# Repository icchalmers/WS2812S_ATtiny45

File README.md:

# WS2812S with ATtiny85

This is a small test board for the WS2812S LEDs using the ATtiny85. It was made as part [Fab Academy 2015](http://www.fabacademy.org/) at [Fab Lab Strathclyde](http://www.strath.ac.uk/fablab/). You can follow the process on [my class website](http://fabacademy.org/archives/2015/eu/students/chalmers.iain/index.html). The content is also mirrored to [my GitHub Pages site](http://icchalmers.github.io/).

# Design

The board was designed in KiCad, and machined on a Denford PCB Engraver. The footprints are designed for reflow soldering, but the board should be hand solderable with a steady hand.

All of the parts are part of the standard Fab Lab inventory, with the exception of the WS2812S and the ATtiny85. However, you can substitute an ATtiny45 without any problem. I just used an 85 because a) more memory and b) we actually got them cheaper!

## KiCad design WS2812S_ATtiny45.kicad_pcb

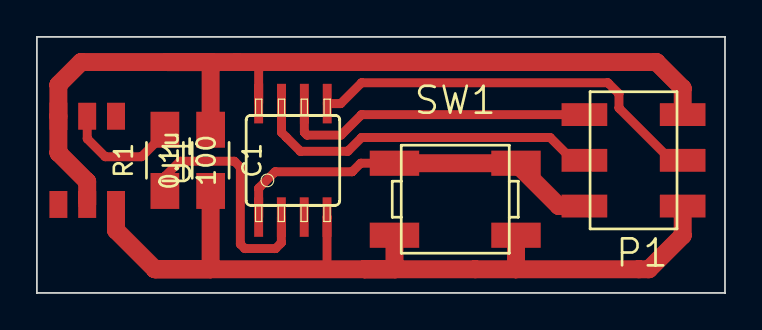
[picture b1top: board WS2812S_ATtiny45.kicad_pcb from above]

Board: 2 copper layers, 38.2 x 14.2 mm, 6 parts (0 on the bottom side), 8 nets.

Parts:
C1: 0.1u; C_1206_HandSoldering_IainEdit
IC1: ATTINY85-S; avr-SOIC8
P1: CONN_02X03; CON_2x3_SMD
R1: 100; C_1206_HandSoldering_IainEdit
SW1: DPST_fixed; PushButton_smd
U1: WS2812S; WS812S

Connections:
GND: C1.2, IC1.4, P1.6, SW1.3, SW1.4, U1.6
unnamed: IC1.1, P1.5, SW1.1, SW1.2
unnamed: IC1.2, R1.1
unnamed: IC1.5, P1.4
unnamed: IC1.6, P1.1
unnamed: IC1.7, P1.3
unnamed: R1.2, U1.2
VDD: C1.1, IC1.8, P1.2, U1.3, U1.5

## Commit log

2015-03-11 fixed typo
